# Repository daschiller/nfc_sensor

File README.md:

# Introduction

Source code and PCB design files for an NFC-enabled sweat sensor.  Published as
part of ["Stretchable and biodegradable batteries with high energy and power
density"](https://doi.org/10.1002/adma.202204457).

# Hardware

The board has been designed in KiCad. You can use it to generate your own Gerbers.

Here's a shortened BOM:

* MCU: ATtiny85V
* NFC tag: ST25DV64K

# Software

Two build systems can be used:

* PlatformIO
* Traditional Makefile using standard toolchain (avr-gcc, avrdude)

I recommend an SOIC-8 clip for flashing.

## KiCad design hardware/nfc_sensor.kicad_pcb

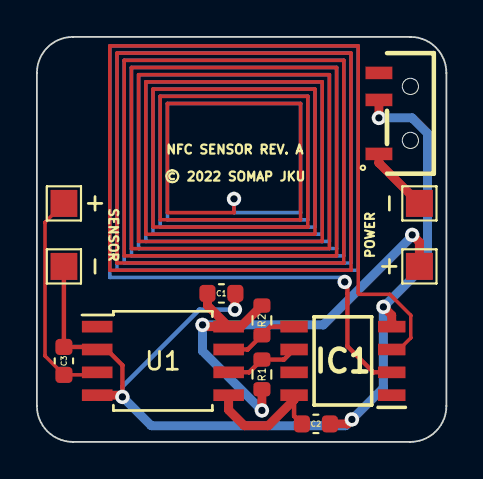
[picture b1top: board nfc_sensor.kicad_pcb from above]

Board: 2 copper layers, 22.8 x 22.5 mm, 12 parts (0 on the bottom side), 6 nets.

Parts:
+: TestPoint_Pad_1.5x1.5mm
+#2: TestPoint_Pad_1.5x1.5mm
-: TestPoint_Pad_1.5x1.5mm
-#2: TestPoint_Pad_1.5x1.5mm
C1: 10u; C_0603_1608Metric
C2: 100n; C_0603_1608Metric
C3: 47n; C_0603_1608Metric
IC1: ST25DV64K-IER6S3; SOIC127P600X175-8N
R1, R2: 4.7k; R_0603_1608Metric
SW1: SSSS810701
U1: ATtiny85V-10SU; SOIC-8W_5.3x5.3mm_P1.27mm

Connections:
+BATT: +.1, C1.1, R1.1, R2.1, U1.8 (VCC)
ADC+: +#2.1, C3.1, U1.3 (XTAL2/PB4)
GND: -.1, -#2.1, C1.2, C2.2, C3.2, IC1.4 (VSS), SW1.1, SW1.2, U1.2 (XTAL1/PB3), U1.4 (GND)
PB1: C2.1, IC1.8 (VCC), U1.5 (AREF/PB0)
SCL: IC1.6 (SCL), R1.2, U1.6 (PB1)
SDA: IC1.5 (SDA), R2.2, U1.7 (PB2)

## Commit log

2022-04-07 Semi-final version
2025-01-26 Add hardware design files and README
2025-01-28 Add license

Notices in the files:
hardware/nfc_sensor.kicad_pcb:
© 2022 SOMAP JKU
